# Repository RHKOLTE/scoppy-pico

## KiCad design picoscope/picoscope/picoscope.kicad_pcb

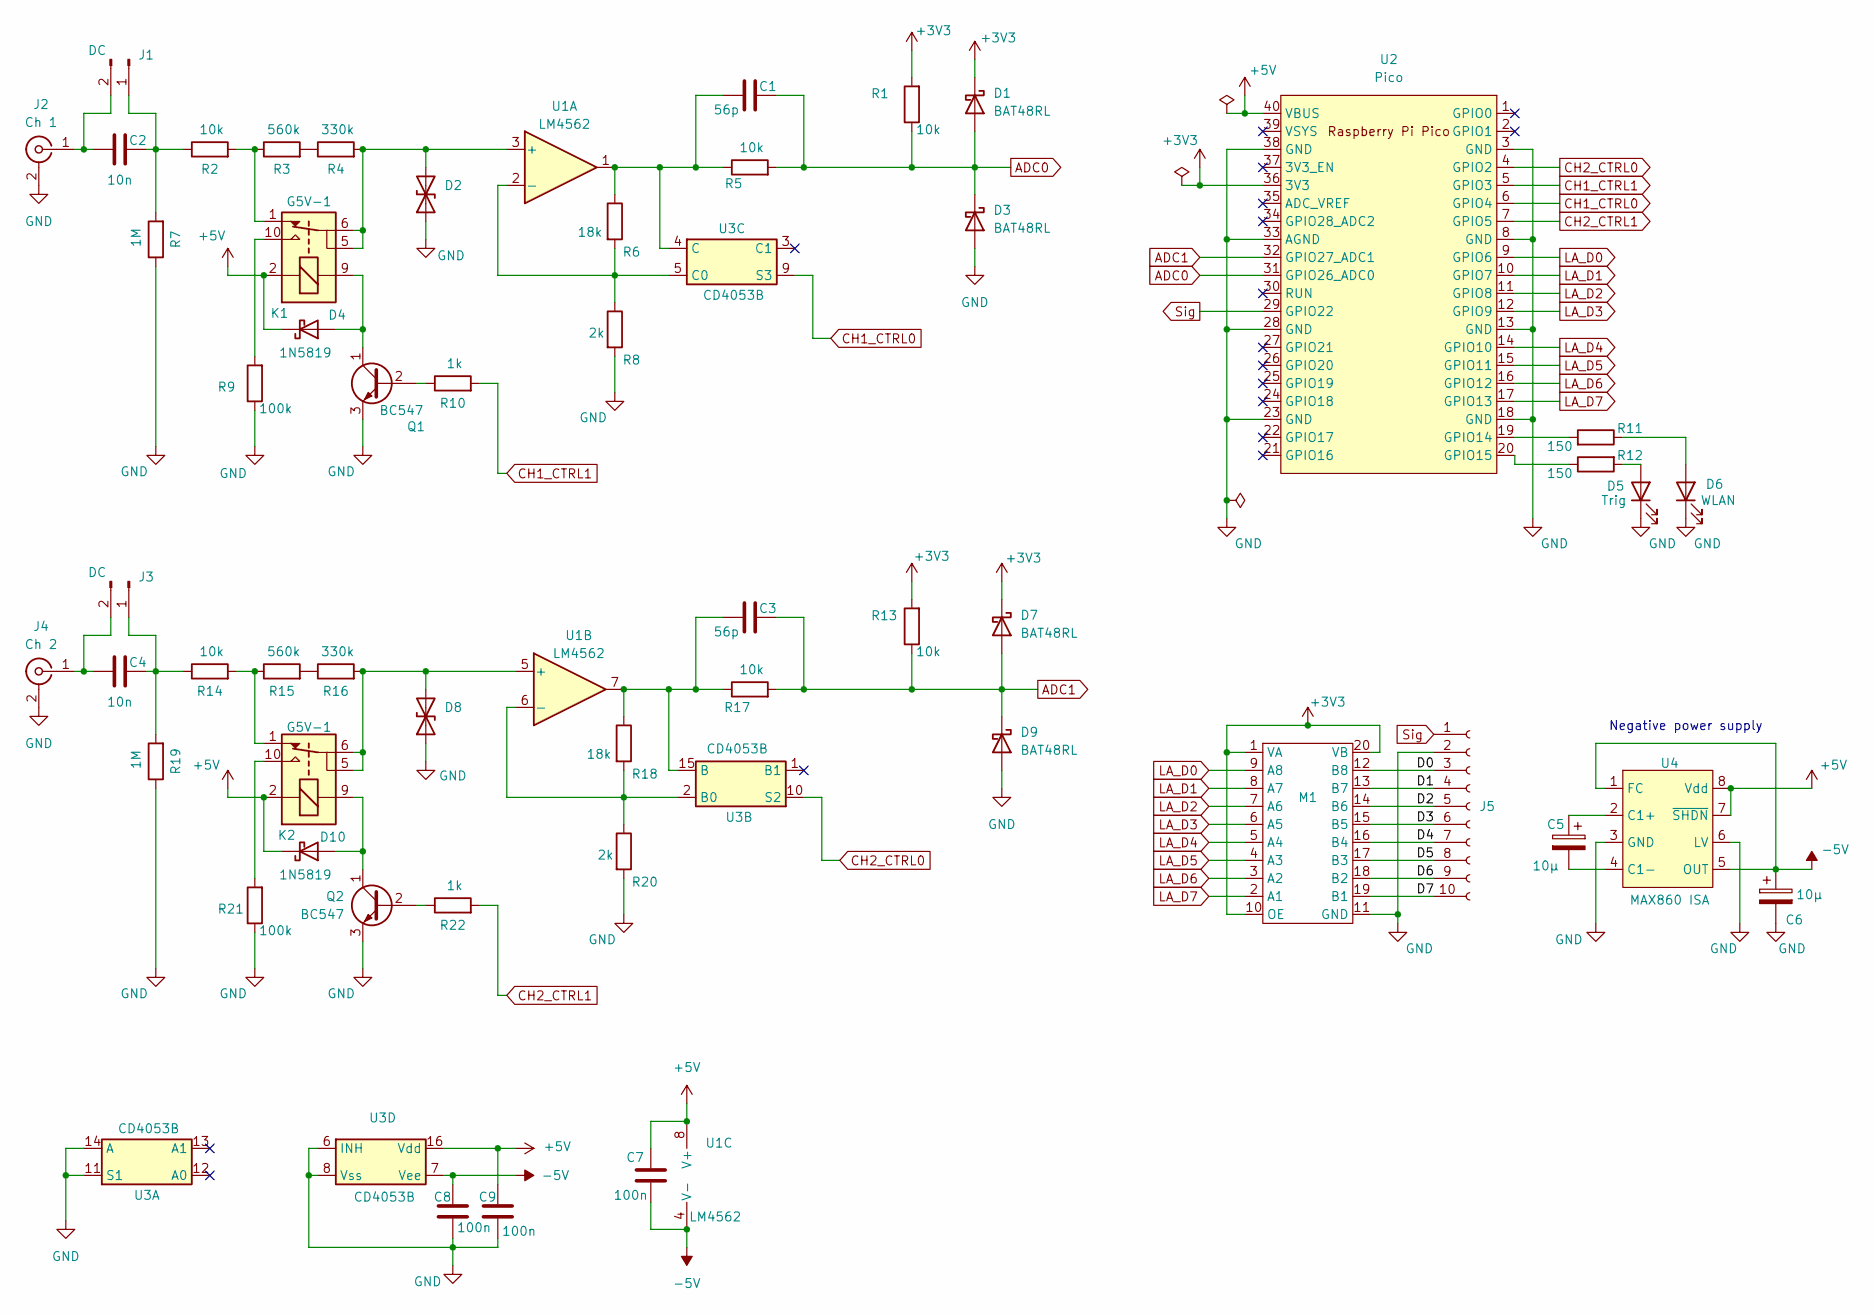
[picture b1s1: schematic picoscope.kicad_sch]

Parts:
C1, C3: 56p; C_Disc_D3.4mm_W2.1mm_P2.50mm
C2: 10n; C_Disc_D3.4mm_W2.1mm_P2.50mm
C4: 10n; C_Disc_D5.0mm_W2.5mm_P2.50mm
C5, C6: 10µ; CP_Radial_D4.0mm_P2.00mm
C7, C8, C9: 100n; C_Disc_D5.0mm_W2.5mm_P5.00mm
D1, D3, D7, D9: BAT48RL; D_DO-35_SOD27_P7.62mm_Horizontal
D2, D8: D5V0F1B2WS; D_SOD-323F
D4, D10: 1N5819; D_DO-41_SOD81_P2.54mm_Vertical_AnodeUp
D5: Trig; LED_D5.0mm
D6: WLAN; LED_D5.0mm
J1, J3: DC; Molex_KK-254_AE-6410-02A_1x02_P2.54mm_Vertical
J2: Ch 1; BNC_Amphenol_UG1094W1
J4: Ch 2; BNC_Amphenol_UG1094W1
J5: Conn_01x10_Socket; PinHeader_1x10_P2.54mm_Vertical
K1, K2: G5V-1; Relay_SPDT_Omron_G5V-1
M1: TXB0108_module
Q1, Q2: BC547; TO-92_Inline
R1, R2, R5, R13, R14, R17: 10k; R_Axial_DIN0207_L6.3mm_D2.5mm_P7.62mm_Horizontal
R3, R15: 560k; R_Axial_DIN0207_L6.3mm_D2.5mm_P7.62mm_Horizontal
R4, R16: 330k; R_Axial_DIN0207_L6.3mm_D2.5mm_P7.62mm_Horizontal
R6, R18: 18k; R_Axial_DIN0207_L6.3mm_D2.5mm_P7.62mm_Horizontal
R7, R19: 1M; R_Axial_DIN0207_L6.3mm_D2.5mm_P7.62mm_Horizontal
R8, R20: 2k; R_Axial_DIN0207_L6.3mm_D2.5mm_P7.62mm_Horizontal
R9, R21: 100k; R_Axial_DIN0207_L6.3mm_D2.5mm_P7.62mm_Horizontal
R10, R22: 1k; R_Axial_DIN0207_L6.3mm_D2.5mm_P7.62mm_Horizontal
R11, R12: 150; R_Axial_DIN0207_L6.3mm_D2.5mm_P7.62mm_Horizontal
U1: LM4562; DIP-8_W7.62mm
U2: Pico; RPi_Pico
U3: CD4053B; DIP-16_W7.62mm
U4: MAX860 ISA; SOIC-8_3.9x4.9mm_P1.27mm

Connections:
+3V3: D1.1 (K), D7.1 (K), M1.1 (VA), M1.10 (OE), M1.20 (VB), R1.2, R13.2, U2.36 (3V3)
+5V: C7.1, C9.1, D4.1 (K), D10.1 (K), K1.2, K2.2, U1.8 (V+), U2.40 (VBUS), U3.16 (Vdd), U4.7 (~SHDN), U4.8 (Vdd)
-5V: C6.1, C7.2, C8.1, U1.4 (V-), U3.7 (Vee), U4.1 (FC), U4.5 (OUT)
/D0: J5.3, M1.12 (B8)
/D1: J5.4, M1.13 (B7)
/D2: J5.5, M1.14 (B6)
/D3: J5.6, M1.15 (B5)
/D4: J5.7, M1.16 (B4)
/D5: J5.8, M1.17 (B3)
/D6: J5.9, M1.18 (B2)
/D7: J5.10, M1.19 (B1)
ADC0: C1.2, D1.2 (A), D3.1 (K), R1.1, R5.2, U2.31 (GPIO26_ADC0)
ADC1: C3.2, D7.2 (A), D9.1 (K), R13.1, R17.2, U2.32 (GPIO27_ADC1)
CH1_CTRL0: U2.6 (GPIO4), U3.9 (S3)
CH1_CTRL1: R10.2, U2.5 (GPIO3)
CH2_CTRL0: U2.4 (GPIO2), U3.10 (S2)
CH2_CTRL1: R22.2, U2.7 (GPIO5)
GND: C6.2, C8.2, C9.2, D2.1 (A1), D3.2 (A), D5.1 (K), D6.1 (K), D8.1 (A1), D9.2 (A), J2.2 (Ext), J4.2 (Ext), J5.2, M1.11 (GND), Q1.3 (E), Q2.3 (E), R7.1, R8.2, R9.1, R19.1, R20.2, R21.1, U2.3 (GND), U2.8 (GND), U2.13 (GND), U2.18 (GND), U2.23 (GND), U2.28 (GND), U2.33 (AGND), U2.38 (GND), U3.6 (INH), U3.8 (Vss), U3.11 (S1), U3.14 (A), U4.3 (GND), U4.6 (LV)
LA_D0: M1.9 (A8), U2.9 (GPIO6)
LA_D1: M1.8 (A7), U2.10 (GPIO7)
LA_D2: M1.7 (A6), U2.11 (GPIO8)
LA_D3: M1.6 (A5), U2.12 (GPIO9)
LA_D4: M1.5 (A4), U2.14 (GPIO10)
LA_D5: M1.4 (A3), U2.15 (GPIO11)
LA_D6: M1.3 (A2), U2.16 (GPIO12)
LA_D7: M1.2 (A1), U2.17 (GPIO13)
unnamed: D2.2 (A2), K1.5, K1.6, R4.2, U1.3 (+)
unnamed: D4.2 (A), K1.9, Q1.1 (C)
unnamed: D5.2 (A), R12.2
unnamed: D6.2 (A), R11.1
unnamed: D8.2 (A2), K2.5, K2.6, R16.2, U1.5 (+)
unnamed: D10.2 (A), K2.9, Q2.1 (C)
unnamed: C2.2, J1.1, R2.1, R7.2
unnamed: C2.1, J1.2, J2.1 (In)
unnamed: C4.2, J3.1, R14.1, R19.2
unnamed: C4.1, J3.2, J4.1 (In)
unnamed: K1.1, R2.2, R3.1
unnamed: K1.10, R9.2
unnamed: K2.1, R14.2, R15.1
unnamed: K2.10, R21.2
unnamed: Q1.2 (B), R10.1
unnamed: Q2.2 (B), R22.1
unnamed: R3.2, R4.1
unnamed: R15.2, R16.1
unnamed: R6.2, R8.1, U1.2 (-), U3.5 (C0)
unnamed: R18.2, R20.1, U1.6 (-), U3.2 (B0)
unnamed: R11.2, U2.19 (GPIO14)
unnamed: R12.1, U2.20 (GPIO15)
unnamed: C3.1, R17.1, R18.1, U1.7, U3.15 (B)
unnamed: C1.1, R5.1, R6.1, U1.1, U3.4 (C)
unnamed: C5.1, U4.2 (C1+)
unnamed: C5.2, U4.4 (C1-)
Sig: J5.1, U2.29 (GPIO22)

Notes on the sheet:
Negative power supply

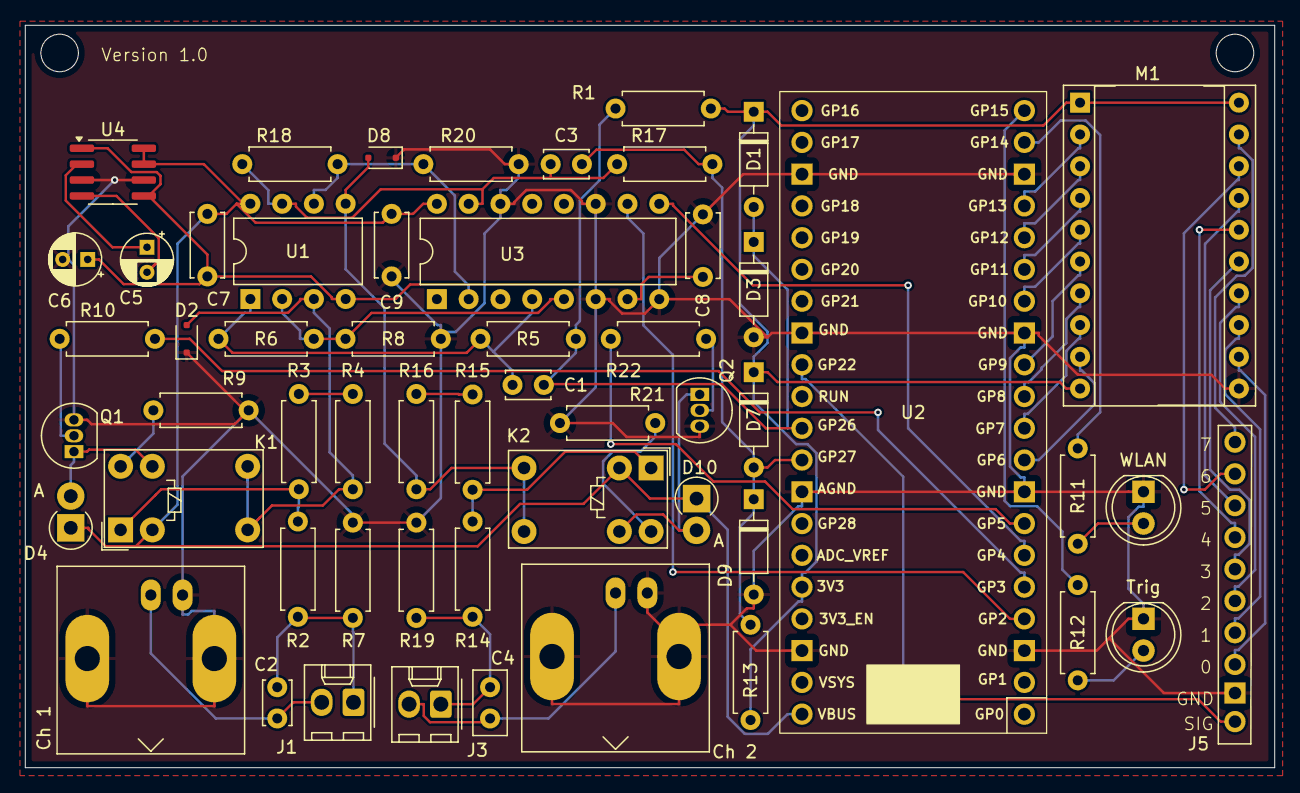
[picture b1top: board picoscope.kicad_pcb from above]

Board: 2 copper layers, 99.9 x 59.4 mm, 55 parts (0 on the bottom side), 53 nets.

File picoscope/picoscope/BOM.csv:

"Reference","Value","Datasheet","Footprint","Qty","DNP"
"C1,C3","56p","~","Capacitor_THT:C_Disc_D3.4mm_W2.1mm_P2.50mm","2",""
"C2,C4","10n","~","-- mixed values --","2",""
"C5,C6","10µ","~","Capacitor_THT:CP_Radial_D4.0mm_P2.00mm","2",""
"C7,C8,C9","100n","~","Capacitor_THT:C_Disc_D5.0mm_W2.5mm_P5.00mm","3",""
"D1,D3,D7,D9","BAT48RL","www.st.com/resource/en/datasheet/bat48.pdf","Diode_THT:D_DO-35_SOD27_P7.62mm_Horizontal","4",""
"D2,D8","D5V0F1B2WS","~","Diode_SMD:D_SOD-323F","2",""
"D4,D10","1N5819","http://www.vishay.com/docs/88525/1n5817.pdf","Diode_THT:D_DO-41_SOD81_P2.54mm_Vertical_AnodeUp","2",""
"D5","Trig","~","LED_THT:LED_D5.0mm","1",""
"D6","WLAN","~","LED_THT:LED_D5.0mm","1",""
"J1,J3","DC","~","Connector_Molex:Molex_KK-254_AE-6410-02A_1x02_P2.54mm_Vertical","2",""
"J2","Ch 1","~","Parts:BNC_Amphenol_UG1094W1","1",""
"J4","Ch 2","~","Parts:BNC_Amphenol_UG1094W1","1",""
"J5","Conn_01x10_Socket","~","Connector_PinHeader_2.54mm:PinHeader_1x10_P2.54mm_Vertical","1",""
"K1,K2","G5V-1","http://omronfs.omron.com/en_US/ecb/products/pdf/en-g5v_1.pdf","Parts:Relay_SPDT_Omron_G5V-1","2",""
"M1","~","","Parts:TXB0108_module","1",""
"Q1,Q2","BC547","https://www.onsemi.com/pub/Collateral/BC550-D.pdf","Package_TO_SOT_THT:TO-92_Inline","2",""
"R1,R2,R5,R13,R14,R17","10k","~","Resistor_THT:R_Axial_DIN0207_L6.3mm_D2.5mm_P7.62mm_Horizontal","6",""
"R3,R15","560k","~","Resistor_THT:R_Axial_DIN0207_L6.3mm_D2.5mm_P7.62mm_Horizontal","2",""
"R4,R16","330k","~","Resistor_THT:R_Axial_DIN0207_L6.3mm_D2.5mm_P7.62mm_Horizontal","2",""
"R6,R18","18k","~","Resistor_THT:R_Axial_DIN0207_L6.3mm_D2.5mm_P7.62mm_Horizontal","2",""
"R7,R19","1M","~","Resistor_THT:R_Axial_DIN0207_L6.3mm_D2.5mm_P7.62mm_Horizontal","2",""
"R8,R20","2k","~","Resistor_THT:R_Axial_DIN0207_L6.3mm_D2.5mm_P7.62mm_Horizontal","2",""
"R9,R21","100k","~","Resistor_THT:R_Axial_DIN0207_L6.3mm_D2.5mm_P7.62mm_Horizontal","2",""
"R10,R22","1k","~","Resistor_THT:R_Axial_DIN0207_L6.3mm_D2.5mm_P7.62mm_Horizontal","2",""
"R11,R12","150","~","Resistor_THT:R_Axial_DIN0207_L6.3mm_D2.5mm_P7.62mm_Horizontal","2",""
"U1","LM4562","http://www.ti.com/lit/ds/symlink/lm4562.pdf","Package_DIP:DIP-8_W7.62mm","1",""
"U2","Pico","","Parts:RPi_Pico","1",""
"U3","CD4053B","http://www.ti.com/lit/ds/symlink/cd4052b.pdf","Package_DIP:DIP-16_W7.62mm","1",""
"U4","MAX860 ISA","","Package_SO:SOIC-8_3.9x4.9mm_P1.27mm","1",""

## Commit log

2025-12-16 Add PICO_SDK_SETUP discovery in CMakeLists.txt
